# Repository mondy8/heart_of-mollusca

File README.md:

# Heart of Mollusca

+ [Heart of Mollusca 紹介動画](https://vimeo.com/240353748)
+ [ADAA アジアデジタルアートアワード 学生インタラクティブアート部門 優秀賞](https://adaa.jp/ja/winners/winners2017.html)
+ [北九州デジタルクリエイターコンテスト2018 入選](https://kdcc.info/archive/2018.html)
+ [ADADA2016 Art paper](https://github.com/ImaokaHiroaki/heart_of-mollusca/blob/master/paper/art_paper.pdf)

 従来のロボットのイメージには「機械的」というキーワードが常に存在していた。ロボットは重厚であり、硬く、冷たいといったイメージである。それゆえに、ロボットには心がない、人間とロボットがコミュニケーションをとることはできない、といった意見が現状では多く見られる。昨今登場したソフトロボティクスという分野は、柔らかいロボットを研究する分野である。ソフトロボティクスを専攻している研究者たちは、「柔らかさ」をテーマにしたロボットを制作することで、何か今までになかったロボットの新しい可能性を探求している。本作品では、従来のロボットのイメージとは異なる有機的な表現を取り入れたロボットを制作することで、今までになかった新たなロボットとのコミュニケーションを実現したいと考えている。

 「Heart of Mollusca」は、人間の心拍とともに動くソフトロボットである。このロボットは、何もしていない状態だと動かず、人の心拍を検知した時、その人の心拍に合わせた動きを始める。鑑賞者はまず、作品の触手の部分にあるパルスセンサーを触る。すると「Heart of Mollusca」の中心部はゆっくりと赤く光りはじめる。そのあと、心拍と共に触手の部分が呼吸をするように膨張・収縮を繰り返す。人差し指で触手を触っているため、心拍にあわせた触手の膨張を感じることができる。「Heart of Mollusca」は、シリコンを使って中から空気を入れることによって動かしている。このシリコンによる柔らかさを用いた軟体動物のような動きは、鑑賞者に独特な感覚をもたらす。
 
 「Heart of Mollusca」を体験した鑑賞者たちは、今まで持っていた従来のロボットとのイメージとの差から興味・関心を抱く人や、ロボットの外見から想像していなかった動きに驚き、生理的な嫌悪感を抱く人など、様々な反応の違いを見せた。有機的な表現を取り入れたことに関しては、心拍とロボットの動きを連動したことにより、ロボットから生命らしさを感じると答えた人が多かった。心拍との連動を取り入れたことに関しては、普段意識することのない自分の心拍を視覚と触覚により体験することで、興味深く感じた人を多く見受けることができた。「Heart of Mollusca」を体験した人たちからは従来のロボットとの触れ合いとは異なった反応が多く得ることができた。

## レシピ

1. シリコン
	+ Ecoflex [(サツク株式会社)](https://vimeo.com/240353748)
	+ DragonSkin [(サツク株式会社)](https://vimeo.com/240353748)
	+ SilPoxy [(サツク株式会社)](https://vimeo.com/240353748)
2. 電気系統
	+ Arduino UNO [(スイッチサイエンス)](https://www.switch-science.com/catalog/789/)
	+ ACアダプター *2 [(robotshop)](https://www.robotshop.com/jp/ja/sfe-power-supply-9vdc-650ma.html?gclid=Cj0KCQiAieTUBRCaARIsAHeLDCRoRLYl_z6s6TUYaBdTTIyXx4kBBwY4bhTE5D_Uc6kAIAWn0mJUxUQaAsiUEALw_wcB)
	+ Arduino用USBケーブル[(robotshop)](https://www.robotshop.com/jp/ja/usb-cable-a-b-arduino.html?gclid=Cj0KCQiAieTUBRCaARIsAHeLDCRSxl-ueeIAc31IGcQsqSDnOyR4DFE949DfWbx3aC_7zmRv_d67dfsaAtkGEALw_wcB)
	+ ソレノイド電磁石バルブ [(amazon)](https://www.amazon.co.jp/uxcell-a14010700ux0271-uxcell-%E3%82%BD%E3%83%AC%E3%83%8E%E3%82%A4%E3%83%89%E9%9B%BB%E7%A3%81%E7%9F%B3%E5%BC%81-%E3%82%BD%E3%83%AC%E3%83%8E%E3%82%A4%E3%83%89%E9%9B%BB%E7%A3%81%E7%9F%B3%E3%83%90%E3%83%AB%E3%83%96-%E7%A9%BA%E6%B0%97%E3%82%AC%E3%82%B9%E3%82%BD%E3%83%AC%E3%83%8E%E3%82%A4%E3%83%89%E3%83%90%E3%83%AB%E3%83%96-DC%E3%83%9E%E3%82%B0%E3%83%8D%E3%83%83%E3%83%88-%E3%82%AA%E3%83%BC%E3%83%97%E3%83%B3%E3%83%95%E3%83%AC%E3%83%BC%E3%83%A0-0-4-0-5kgf-cm2-2-6V/dp/B00JR3ZQSC/ref=pd_sbs_328_19?_encoding=UTF8&psc=1&refRID=D9Q86W53MPAES85V7PW6)
	+ 気圧センサー MIS-2500-015G [(秋月)](http://akizukidenshi.com/catalog/g/gP-07272/)
	+ 心拍センサー [(スイッチサイエンス)](https://www.switch-science.com/catalog/1135/)
	+ Mitsumi マイクロエアポンプ [(amazon)](https://www.amazon.co.jp/Mitsumi-R-14-%E3%83%9E%E3%82%A4%E3%82%AF%E3%83%AD%E3%82%A8%E3%82%A2%E3%83%9D%E3%83%B3%E3%83%97-200mA-%E3%83%9F%E3%83%8B%E3%83%9D%E3%83%B3%E3%83%97/dp/B01H6VHRDS/ref=sr_1_1?ie=UTF8&qid=1492408470&sr=8-1&keywords=mitsumi)
	+ 2Aデュアルモーターコントローラー [(秋月)](http://akizukidenshi.com/catalog/g/gM-06680/)
3. 小物系
	+ シリコンチューブ 4mm x 6mm [(モノタロウ)](https://www.monotaro.com/g/00250063/)
	+ シリコンチューブコネクター (二方型・クロス型・T型) [(モノタロウ)](https://www.monotaro.com/p/8933/4497/)
	+ PP ディスクカップ [(モノタロウ)](https://www.monotaro.com/p/5843/8712/?t.q=%83%7E%83L%83V%83%93%83O%83J%83b%83v)
	+ 極薄ニトリルゴム手袋 [(モノタロウ)](https://www.monotaro.com/g/00277898/?t.q=%8E%E8%91%DC)
	+ アルミ丸パイプ [(モノタロウ)](https://www.monotaro.com/g/00280306/)
	+ テルモシリンジ [(モノタロウ)](https://www.monotaro.com/p/0292/1861/?t.q=%83V%83%8A%83%93%83W)
	+ 割り箸
	+ 計量器
	
4. 設備
	+ 真空チャンバー
	+ オーブン
	+ 3Dプリンター
	+ CNCミリングマシン（基板切削用）
	
## Arduino配線図

## 3Dデータ素材

* 球体上部分
* 球体下部分
* Ecoflex用フタ部分
* Ecoflex用土台
* DragonSkin用土台

## Eagle切削基板

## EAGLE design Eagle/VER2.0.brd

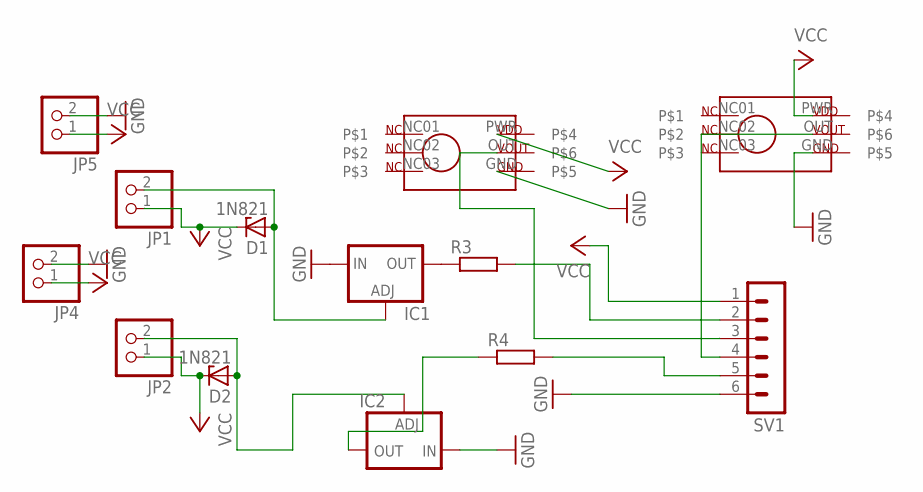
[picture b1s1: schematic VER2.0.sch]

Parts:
D1, D2: 1N821; DO35Z10
IC1, IC2: LM317TS; 317TS
JP1, JP2, JP4, JP5: PINHD-1X2; 1X02
R3, R4: R-EU_0207/10; 0207/10
SV1: MA06-1
U$1, U$2: MIS-2500

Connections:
GND: IC1.3 (IN), IC2.3 (IN), JP4.2, JP5.2, SV1.6, U$1.GND, U$2.GND
unnamed: R3.2, SV1.2
unnamed: SV1.3, U$1.OUT
unnamed: IC2.2 (OUT), R4.1
unnamed: D2.A, IC2.1 (ADJ), JP2.2
unnamed: IC1.2 (OUT), R3.1
unnamed: D1.A, IC1.1 (ADJ), JP1.2
unnamed: SV1.4, U$2.OUT
unnamed: R4.2, SV1.5
VCC: D1.C, D2.C, JP1.1, JP2.1, JP4.1, JP5.1, SV1.1, U$1.PWR, U$2.PWR

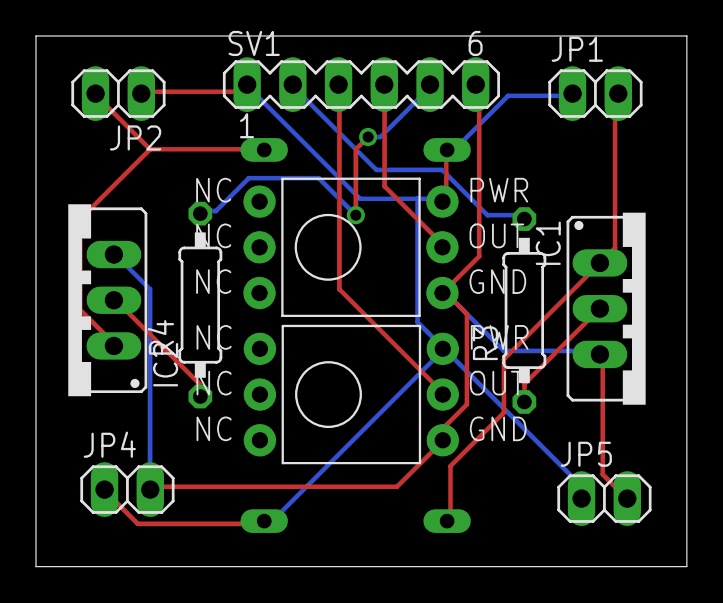
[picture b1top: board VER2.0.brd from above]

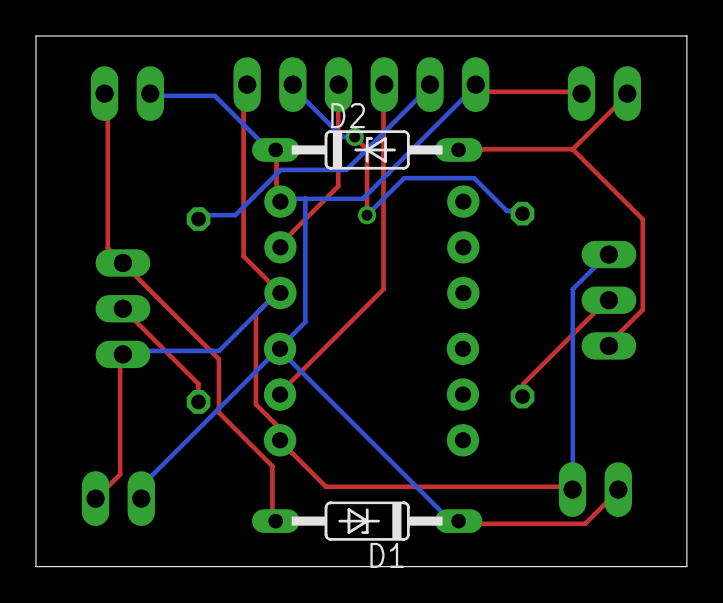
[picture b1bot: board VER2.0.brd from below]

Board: 2 copper layers, 36.2 x 29.5 mm, 13 parts (2 on the bottom side), 10 nets.

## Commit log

2018-03-03 3Ddata更新、eagle説明更新
2018-03-03 3D説明更新
2018-03-03 説明更新
2024-04-05 Art Paper追加
2024-04-05 リンク修正
